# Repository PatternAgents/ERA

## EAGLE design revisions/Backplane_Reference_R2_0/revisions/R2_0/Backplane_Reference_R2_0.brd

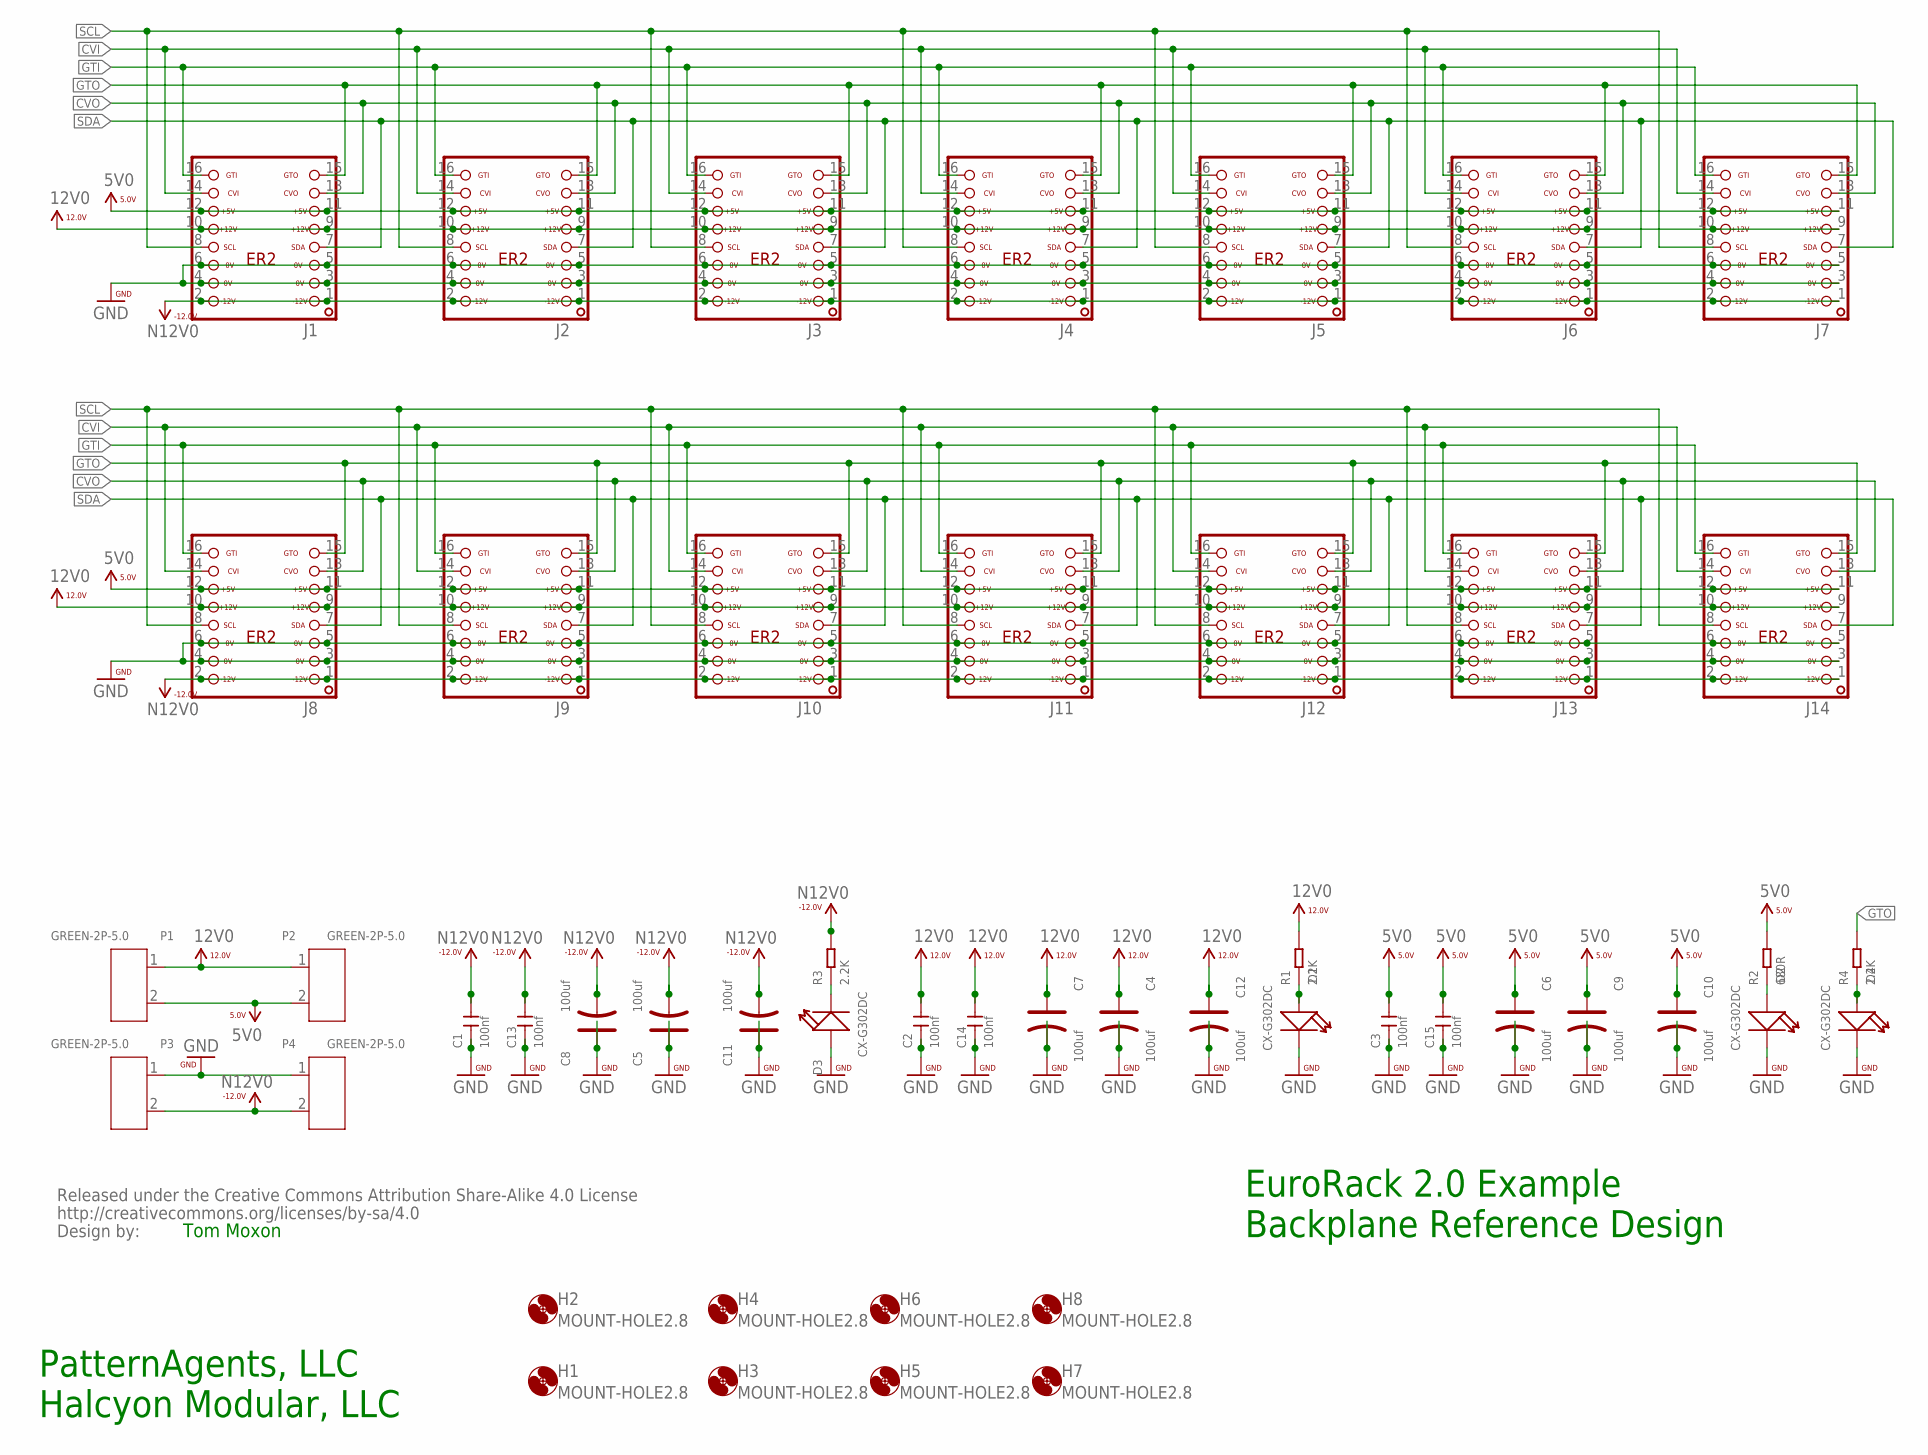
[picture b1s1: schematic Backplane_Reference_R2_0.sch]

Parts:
C1, C2, C3, C13, C14, C15: 100nf; CERAMIC-2.54
C4, C5, C6, C7, C8, C9, C10, C11, C12: 100uf; PC-D5.3MM
D1, D2, D3, D4: CX-G302DC; LED2-2.54-D3.0MM
H1, H2, H3, H4, H5, H6, H7, H8: MOUNT-HOLE2.8; 2,8
J1, J2, J3, J4, J5, J6, J7, J8, J9, J10, J11, J12, J13, J14: ER2-SHROUD; ER2
P1, P2, P3, P4: GREEN-2P-5.0; H2-5.0-10.5X8.0MM
R1, R3, R4: 2.2K; PR-D2.3XL6.5MM
R2: 680R; PR-D2.3XL6.5MM
U$48: BY_CC_SA_TEXTTEXT; BY_CC_SA_TEXT

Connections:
5V0: C3.2, C6.+, C9.+, C10.+, C15.2, J1.11, J1.12, J2.11, J2.12, J3.11, J3.12, J4.11, J4.12, J5.11, J5.12, J6.11, J6.12, J7.11, J7.12, J8.11, J8.12, J9.11, J9.12, J10.11, J10.12, J11.11, J11.12, J12.11, J12.12, J13.11, J13.12, J14.11, J14.12, P1.2, P2.2, R2.2
12V0: C2.2, C4.+, C7.+, C12.+, C14.2, J1.9, J1.10, J2.9, J2.10, J3.9, J3.10, J4.9, J4.10, J5.9, J5.10, J6.9, J6.10, J7.9, J7.10, J8.9, J8.10, J9.9, J9.10, J10.9, J10.10, J11.9, J11.10, J12.9, J12.10, J13.9, J13.10, J14.9, J14.10, P1.1, P2.1, R1.2
CVI: J1.14, J2.14, J3.14, J4.14, J5.14, J6.14, J7.14, J8.14, J9.14, J10.14, J11.14, J12.14, J13.14, J14.14
CVO: J1.13, J2.13, J3.13, J4.13, J5.13, J6.13, J7.13, J8.13, J9.13, J10.13, J11.13, J12.13, J13.13, J14.13
GND: C1.1, C2.1, C3.1, C4.-, C5.+, C6.-, C7.-, C8.+, C9.-, C10.-, C11.+, C12.-, C13.1, C14.1, C15.1, D1.K (-), D2.K (-), D3.A (+), D4.K (-), J1.3, J1.4, J1.5, J1.6, J2.3, J2.4, J2.5, J2.6, J3.3, J3.4, J3.5, J3.6, J4.3, J4.4, J4.5, J4.6, J5.3, J5.4, J5.5, J5.6, J6.3, J6.4, J6.5, J6.6, J7.3, J7.4, J7.5, J7.6, J8.3, J8.4, J8.5, J8.6, J9.3, J9.4, J9.5, J9.6, J10.3, J10.4, J10.5, J10.6, J11.3, J11.4, J11.5, J11.6, J12.3, J12.4, J12.5, J12.6, J13.3, J13.4, J13.5, J13.6, J14.3, J14.4, J14.5, J14.6, P3.1, P4.1
GTI: J1.16, J2.16, J3.16, J4.16, J5.16, J6.16, J7.16, J8.16, J9.16, J10.16, J11.16, J12.16, J13.16, J14.16
GTO: J1.15, J2.15, J3.15, J4.15, J5.15, J6.15, J7.15, J8.15, J9.15, J10.15, J11.15, J12.15, J13.15, J14.15, R4.2
N12V0: C1.2, C5.-, C8.-, C11.-, C13.2, J1.1, J1.2, J2.1, J2.2, J3.1, J3.2, J4.1, J4.2, J5.1, J5.2, J6.1, J6.2, J7.1, J7.2, J8.1, J8.2, J9.1, J9.2, J10.1, J10.2, J11.1, J11.2, J12.1, J12.2, J13.1, J13.2, J14.1, J14.2, P3.2, P4.2, R3.2
unnamed: D3.K (-), R3.1
unnamed: D1.A (+), R1.1
unnamed: D2.A (+), R2.1
unnamed: D4.A (+), R4.1
SCL: J1.8, J2.8, J3.8, J4.8, J5.8, J6.8, J7.8, J8.8, J9.8, J10.8, J11.8, J12.8, J13.8, J14.8
SDA: J1.7, J2.7, J3.7, J4.7, J5.7, J6.7, J7.7, J8.7, J9.7, J10.7, J11.7, J12.7, J13.7, J14.7

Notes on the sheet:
EuroRack 2.0 Example Backplane Reference Design
PatternAgents, LLC Halcyon Modular, LLC
Tom Moxon

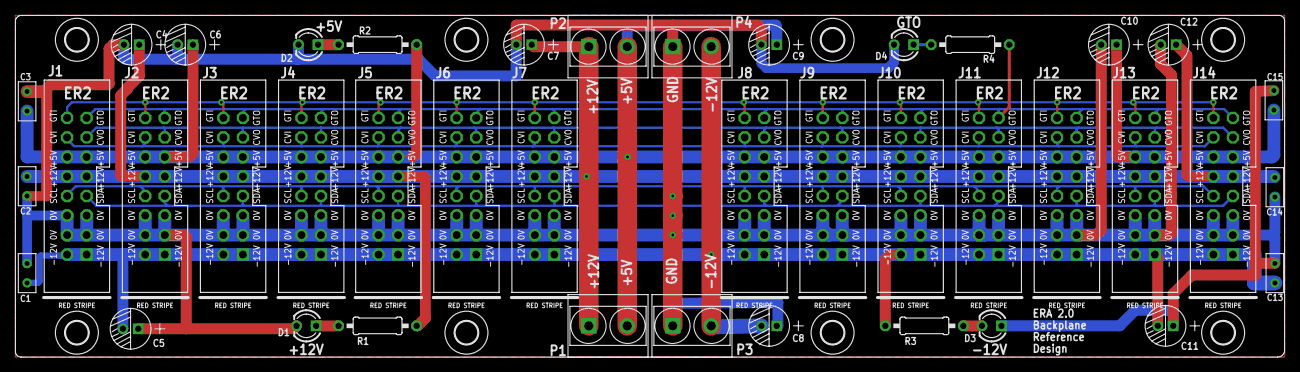
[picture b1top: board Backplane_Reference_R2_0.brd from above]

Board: 2 copper layers, 165.1 x 44.5 mm, 50 parts (0 on the bottom side), 14 nets.

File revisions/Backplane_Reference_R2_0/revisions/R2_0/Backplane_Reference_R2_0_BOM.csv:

6,100nf,DIP-CERAMIC-DISC-100NF-50V-Y5V(D5.0MM),CERAMIC-2.54,"C1, C2, C3, C13, C14, C15",302010208,CC1-F5SL2A101KSPW,100nf
9,100uf,DIP-ALUMINUM-100UF-16V(D5-H7MM),PC-D5.3MM,"C4, C5, C6, C7, C8, C9, C10, C11, C12",302030031,KS 100uF/16V,100uf
3,2.2K,DIP-RES-2.2K-5%-1/4W(PR-D2.3XL6.5MM),PR-D2.3XL6.5MM,"R1, R3, R4",301020010,FHCFR-1/4W-222J,2.2K
1,680R,DIP-RES-680R-5%-1/4W(PR-D2.3XL6.5MM),PR-D2.3XL6.5MM,R2,301020007,FHCFR-1/4W-681J,680R
4,CX-G302DC,DIP-LED-GREEN-GREEN(2P-D3MM),LED2-2.54-D3.0MM,"D1, D2, D3, D4",304090040,CX-G302DC,CX-G302DC
14,ER2-SHROUD,ER2-SHROUD,ER2-SHROUD,"J1, J2, J3, J4, J5, J6, J7, J8, J9, J10, J11, J12, J13, J14",302-S161,302-S161,302-S161
4,GREEN-2P-5.0,SCREW-TERMINAL-GREEN(2P-5.0),H2-5.0-10.5X8.0MM,"P1, P2, P3, P4",320110031,1935161,GREEN-2P-5.0

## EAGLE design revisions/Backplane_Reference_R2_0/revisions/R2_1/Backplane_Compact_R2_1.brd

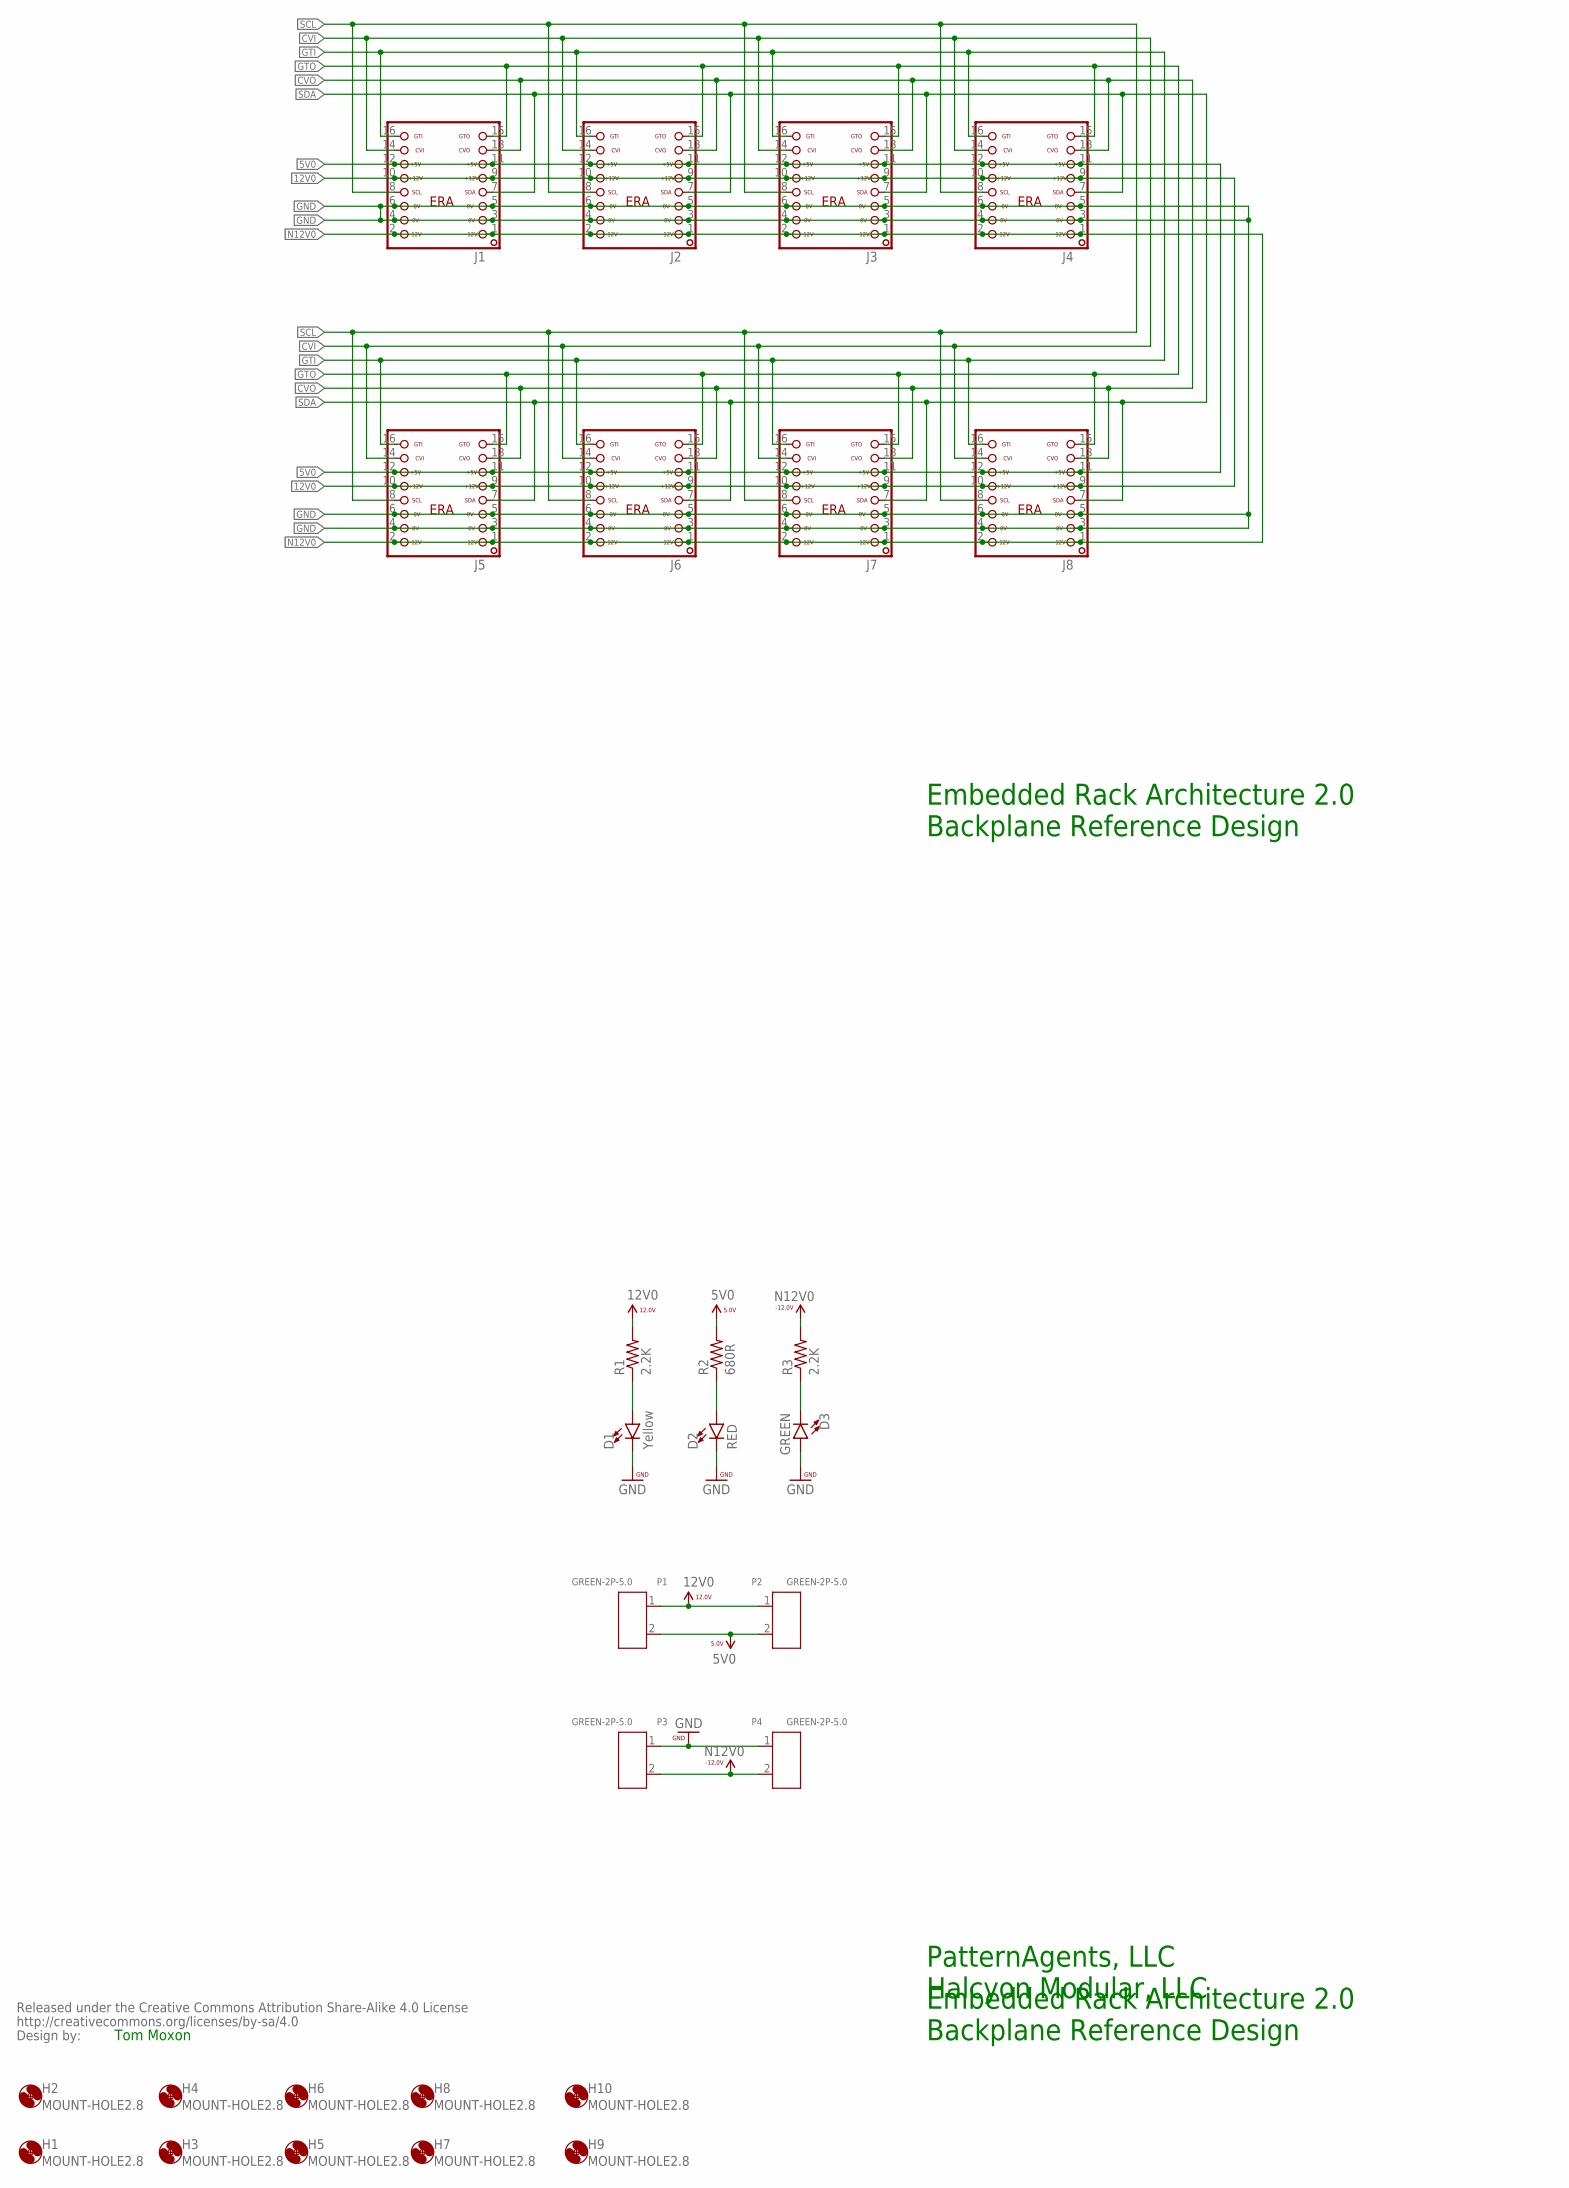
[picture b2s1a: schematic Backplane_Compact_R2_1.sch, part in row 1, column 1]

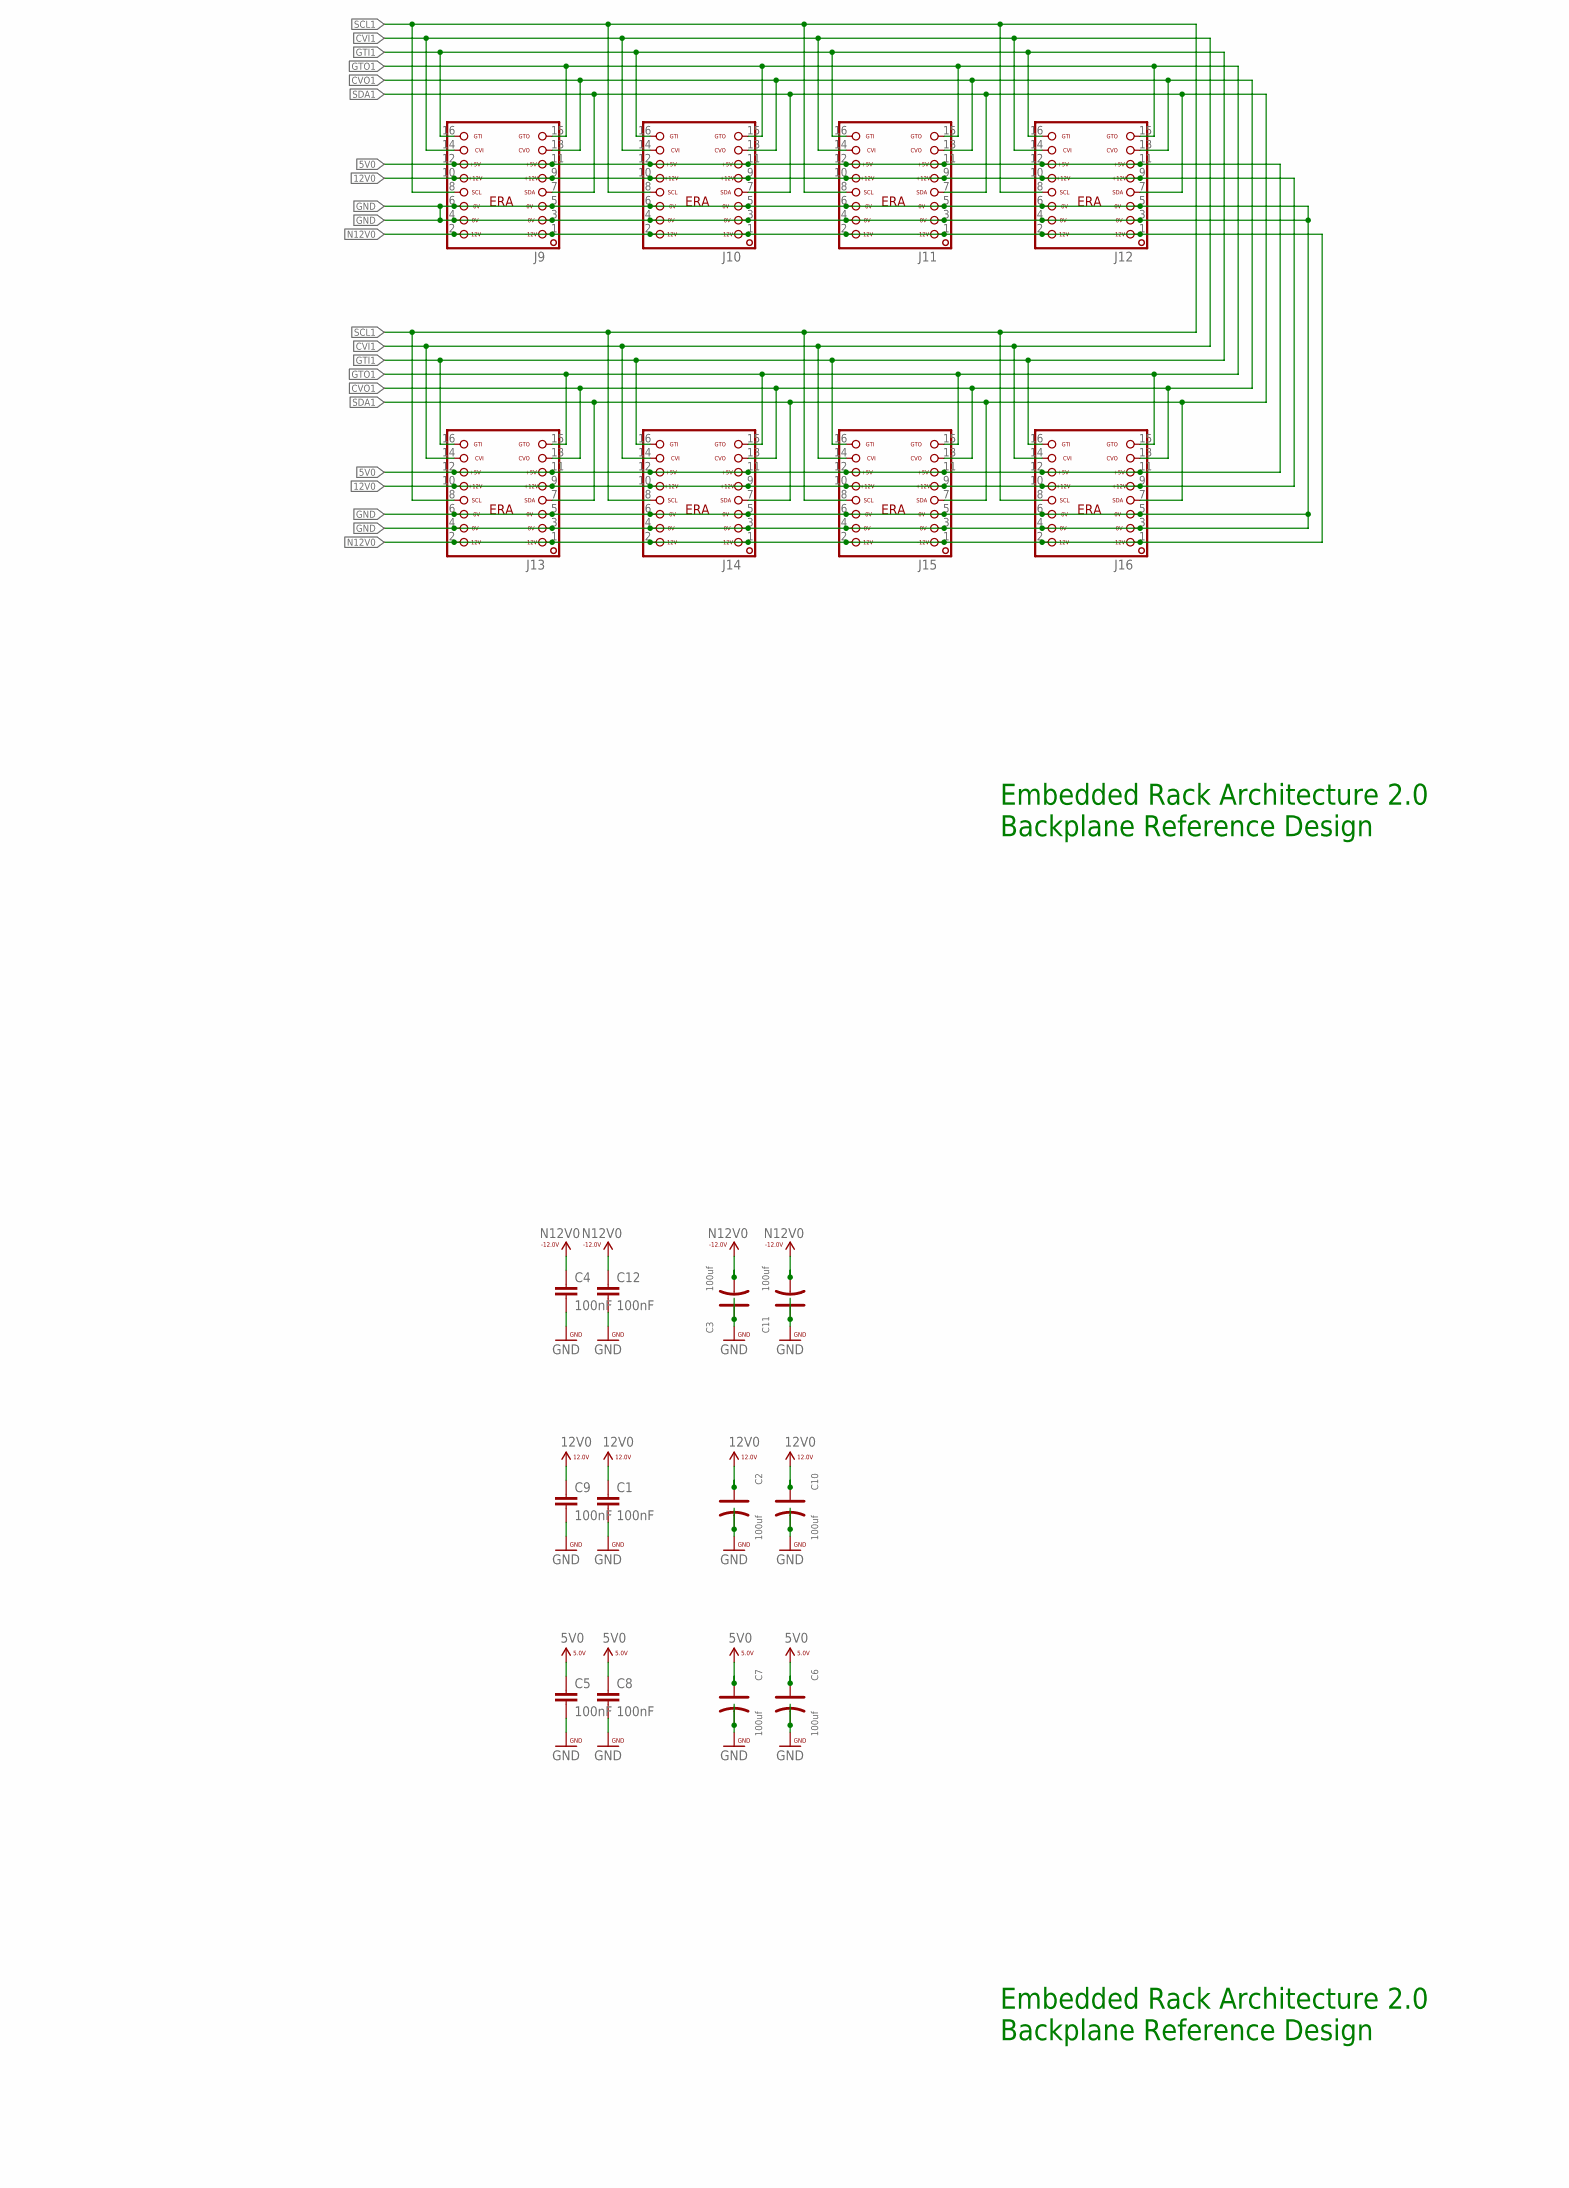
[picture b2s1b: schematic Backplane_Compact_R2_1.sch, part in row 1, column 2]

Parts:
C1, C4, C5, C8, C9, C12: 100nF; 0603-CAP
C2, C3, C6, C7, C10, C11: 100uf; PC-D5.3MM
D1: Yellow; LED-0603
D2: RED; LED-0603
D3: GREEN; LED-0603
H1, H2, H3, H4, H5, H6, H7, H8, H9, H10: MOUNT-HOLE2.8; 2,8
J1, J2, J3, J4, J5, J6, J7, J8, J9, J10, J11, J12, J13, J14, J15, J16: ERA-SHROUD; ERA
P1, P2, P3, P4: GREEN-2P-5.0; H2-5.0-10.5X8.0MM
R1, R3: 2.2K; 0603-RES
R2: 680R; 0603-RES
U$48: BY_CC_SA_TEXTTEXT; BY_CC_SA_TEXT

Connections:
5V0: C5.1, C6.+, C7.+, C8.1, J1.11, J1.12, J2.11, J2.12, J3.11, J3.12, J4.11, J4.12, J5.11, J5.12, J6.11, J6.12, J7.11, J7.12, J8.11, J8.12, J9.11, J9.12, J10.11, J10.12, J11.11, J11.12, J12.11, J12.12, J13.11, J13.12, J14.11, J14.12, J15.11, J15.12, J16.11, J16.12, P1.2, P2.2, R2.2
12V0: C1.1, C2.+, C9.1, C10.+, J1.9, J1.10, J2.9, J2.10, J3.9, J3.10, J4.9, J4.10, J5.9, J5.10, J6.9, J6.10, J7.9, J7.10, J8.9, J8.10, J9.9, J9.10, J10.9, J10.10, J11.9, J11.10, J12.9, J12.10, J13.9, J13.10, J14.9, J14.10, J15.9, J15.10, J16.9, J16.10, P1.1, P2.1, R1.2
CVI: J1.14, J2.14, J3.14, J4.14, J5.14, J6.14, J7.14, J8.14
CVI1: J9.14, J10.14, J11.14, J12.14, J13.14, J14.14, J15.14, J16.14
CVO: J1.13, J2.13, J3.13, J4.13, J5.13, J6.13, J7.13, J8.13
CVO1: J9.13, J10.13, J11.13, J12.13, J13.13, J14.13, J15.13, J16.13
GND: C1.2, C2.-, C3.+, C4.2, C5.2, C6.-, C7.-, C8.2, C9.2, C10.-, C11.+, C12.2, D1.C, D2.C, D3.A, J1.3, J1.4, J1.5, J1.6, J2.3, J2.4, J2.5, J2.6, J3.3, J3.4, J3.5, J3.6, J4.3, J4.4, J4.5, J4.6, J5.3, J5.4, J5.5, J5.6, J6.3, J6.4, J6.5, J6.6, J7.3, J7.4, J7.5, J7.6, J8.3, J8.4, J8.5, J8.6, J9.3, J9.4, J9.5, J9.6, J10.3, J10.4, J10.5, J10.6, J11.3, J11.4, J11.5, J11.6, J12.3, J12.4, J12.5, J12.6, J13.3, J13.4, J13.5, J13.6, J14.3, J14.4, J14.5, J14.6, J15.3, J15.4, J15.5, J15.6, J16.3, J16.4, J16.5, J16.6, P3.1, P4.1
GREEN: D3.C, R3.1
GTI: J1.16, J2.16, J3.16, J4.16, J5.16, J6.16, J7.16, J8.16
GTI1: J9.16, J10.16, J11.16, J12.16, J13.16, J14.16, J15.16, J16.16
GTO: J1.15, J2.15, J3.15, J4.15, J5.15, J6.15, J7.15, J8.15
GTO1: J9.15, J10.15, J11.15, J12.15, J13.15, J14.15, J15.15, J16.15
N12V0: C3.-, C4.1, C11.-, C12.1, J1.1, J1.2, J2.1, J2.2, J3.1, J3.2, J4.1, J4.2, J5.1, J5.2, J6.1, J6.2, J7.1, J7.2, J8.1, J8.2, J9.1, J9.2, J10.1, J10.2, J11.1, J11.2, J12.1, J12.2, J13.1, J13.2, J14.1, J14.2, J15.1, J15.2, J16.1, J16.2, P3.2, P4.2, R3.2
RED: D2.A, R2.1
SCL: J1.8, J2.8, J3.8, J4.8, J5.8, J6.8, J7.8, J8.8
SCL1: J9.8, J10.8, J11.8, J12.8, J13.8, J14.8, J15.8, J16.8
SDA: J1.7, J2.7, J3.7, J4.7, J5.7, J6.7, J7.7, J8.7
SDA1: J9.7, J10.7, J11.7, J12.7, J13.7, J14.7, J15.7, J16.7
YELLOW: D1.A, R1.1

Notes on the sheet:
Embedded Rack Architecture 2.0 Backplane Reference Design
PatternAgents, LLC Halcyon Modular, LLC
Tom Moxon

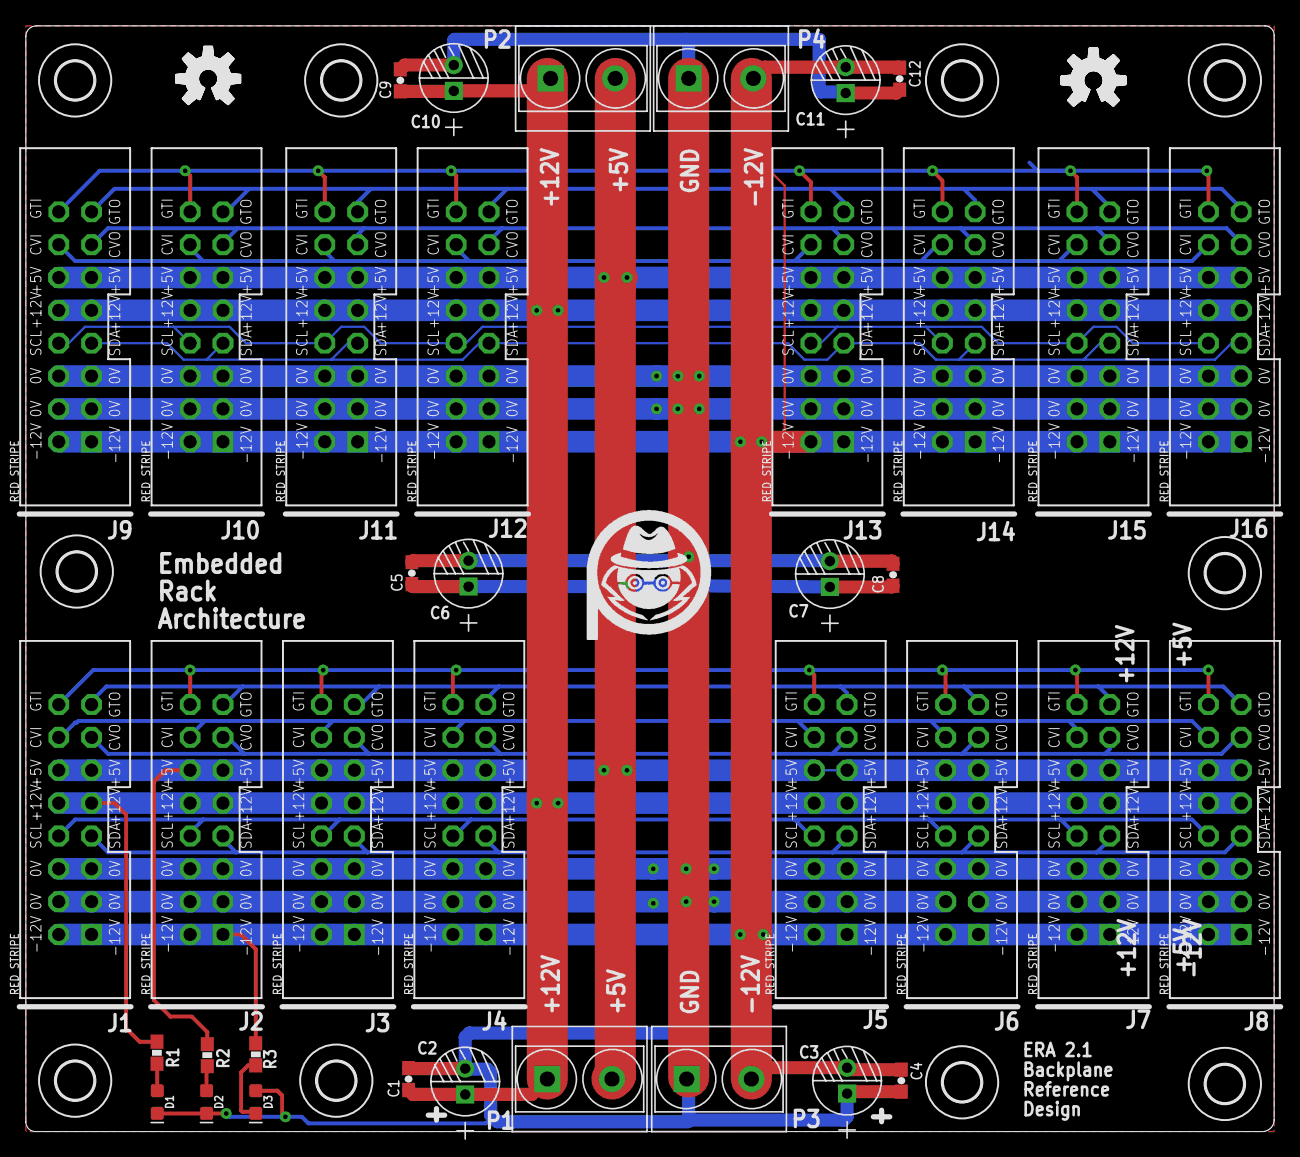
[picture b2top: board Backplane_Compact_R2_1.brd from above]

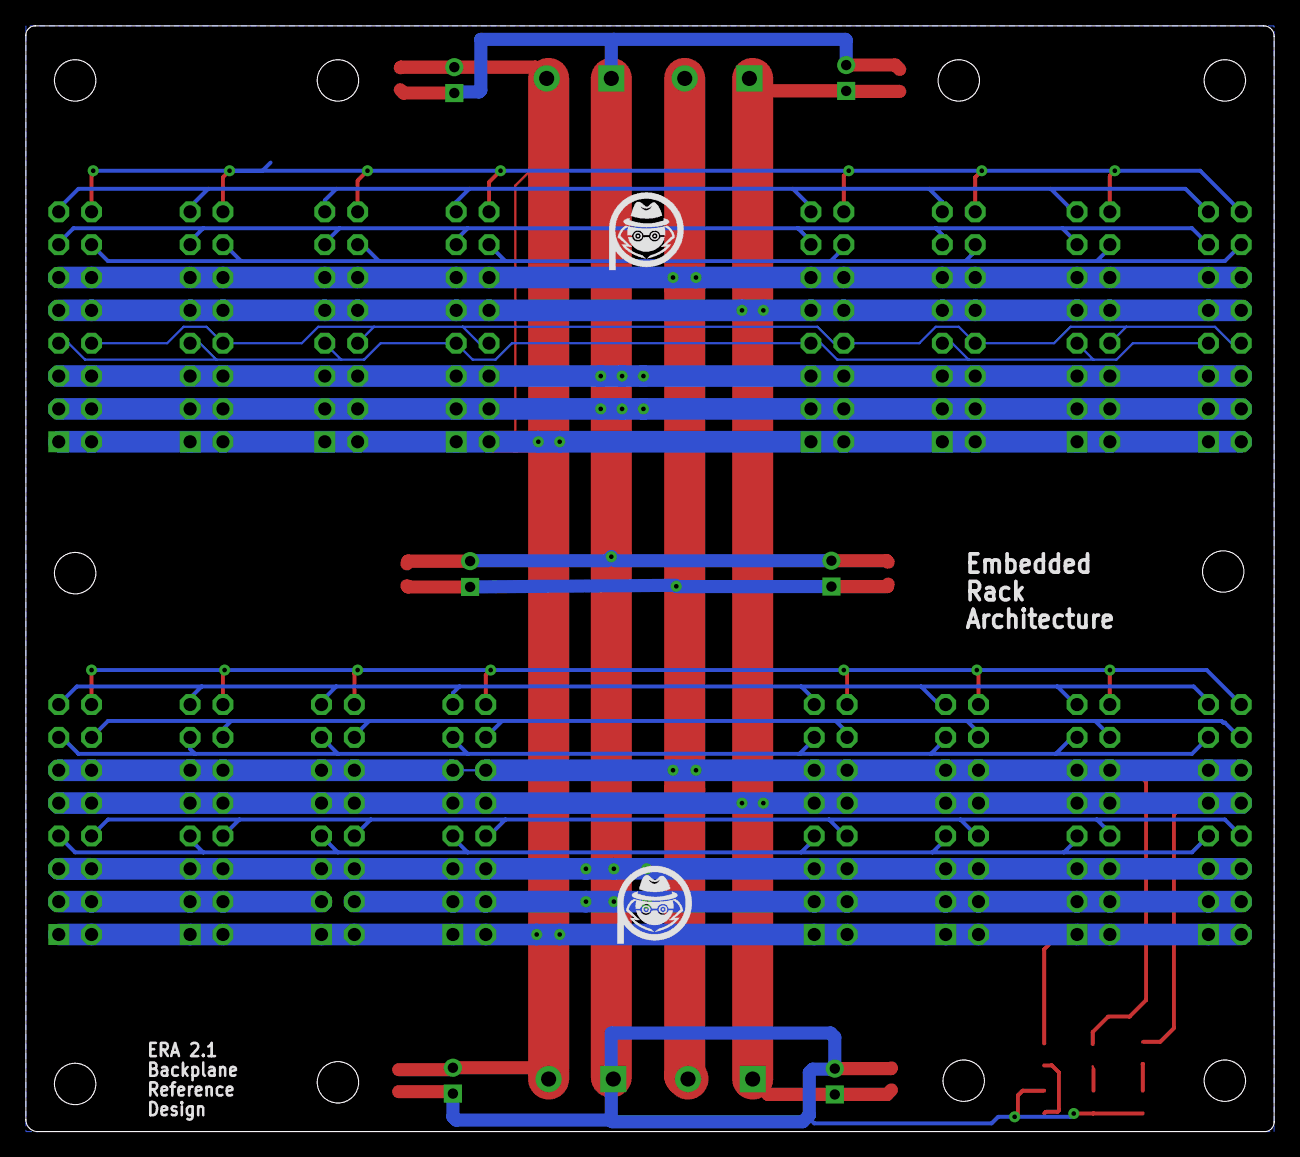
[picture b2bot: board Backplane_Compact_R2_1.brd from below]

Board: 2 copper layers, 96.5 x 85.5 mm, 56 parts (2 on the bottom side), 19 nets.

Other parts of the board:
U$7, U$8, U$9, U$36: OSHW_LOGO_MED_SYM
U$19, U$37: PA_LOGO_SYMMED; PA_LOGO_AGENT_MED_SYM
U$38: PA_LOGO_SYMLARGE; PA_LOGO_AGENT_LRG_SYM

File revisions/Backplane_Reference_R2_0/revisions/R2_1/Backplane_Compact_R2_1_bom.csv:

"Qty";"Value";"Device";"Package";"Parts";"Description";"";
"6";"100nF";"CAP0603-CAP";"0603-CAP";"C1, C4, C5, C8, C9, C12";"Capacitor";"";
"6";"100uf";"DIP-ALUMINUM-100UF-16V(D5-H7MM)";"PC-D5.3MM";"C2, C3, C6, C7, C10, C11";"302030031";"";
"2";"2.2K";"RESISTOR0603";"0603-RES";"R1, R3";"Resistor";"";
"1";"680R";"RESISTOR0603";"0603-RES";"R2";"Resistor";"";
"1";"BY_CC_SA_TEXTTEXT";"BY_CC_SA_TEXTTEXT";"BY_CC_SA_TEXT";"U$48";"BY_CC_SA_TEXT";"";
"16";"ERA-SHROUD";"ERA-SHROUD";"ERA";"J1, J2, J3, J4, J5, J6, J7, J8, J9, J10, J11, J12, J13, J14, J15, J16";"EuroRack2 - Backplane Connector";"";
"1";"GREEN";"LED-GREEN0603";"LED-0603";"D3";"Green SMD LED";"";
"4";"GREEN-2P-5.0";"SCREW-TERMINAL-GREEN(2P-5.0)";"H2-5.0-10.5X8.0MM";"P1, P2, P3, P4";"320110031";"";
"10";"MOUNT-HOLE2.8";"MOUNT-HOLE2.8";"2,8";"H1, H2, H3, H4, H5, H6, H7, H8, H9, H10";"MOUNTING HOLE with drill center marker";"";
"1";"RED";"LED-RED0603";"LED-0603";"D2";"Red SMD LED";"";
"1";"Yellow";"LED-YELLOW0603";"LED-0603";"D1";"Yellow SMD LED";"";

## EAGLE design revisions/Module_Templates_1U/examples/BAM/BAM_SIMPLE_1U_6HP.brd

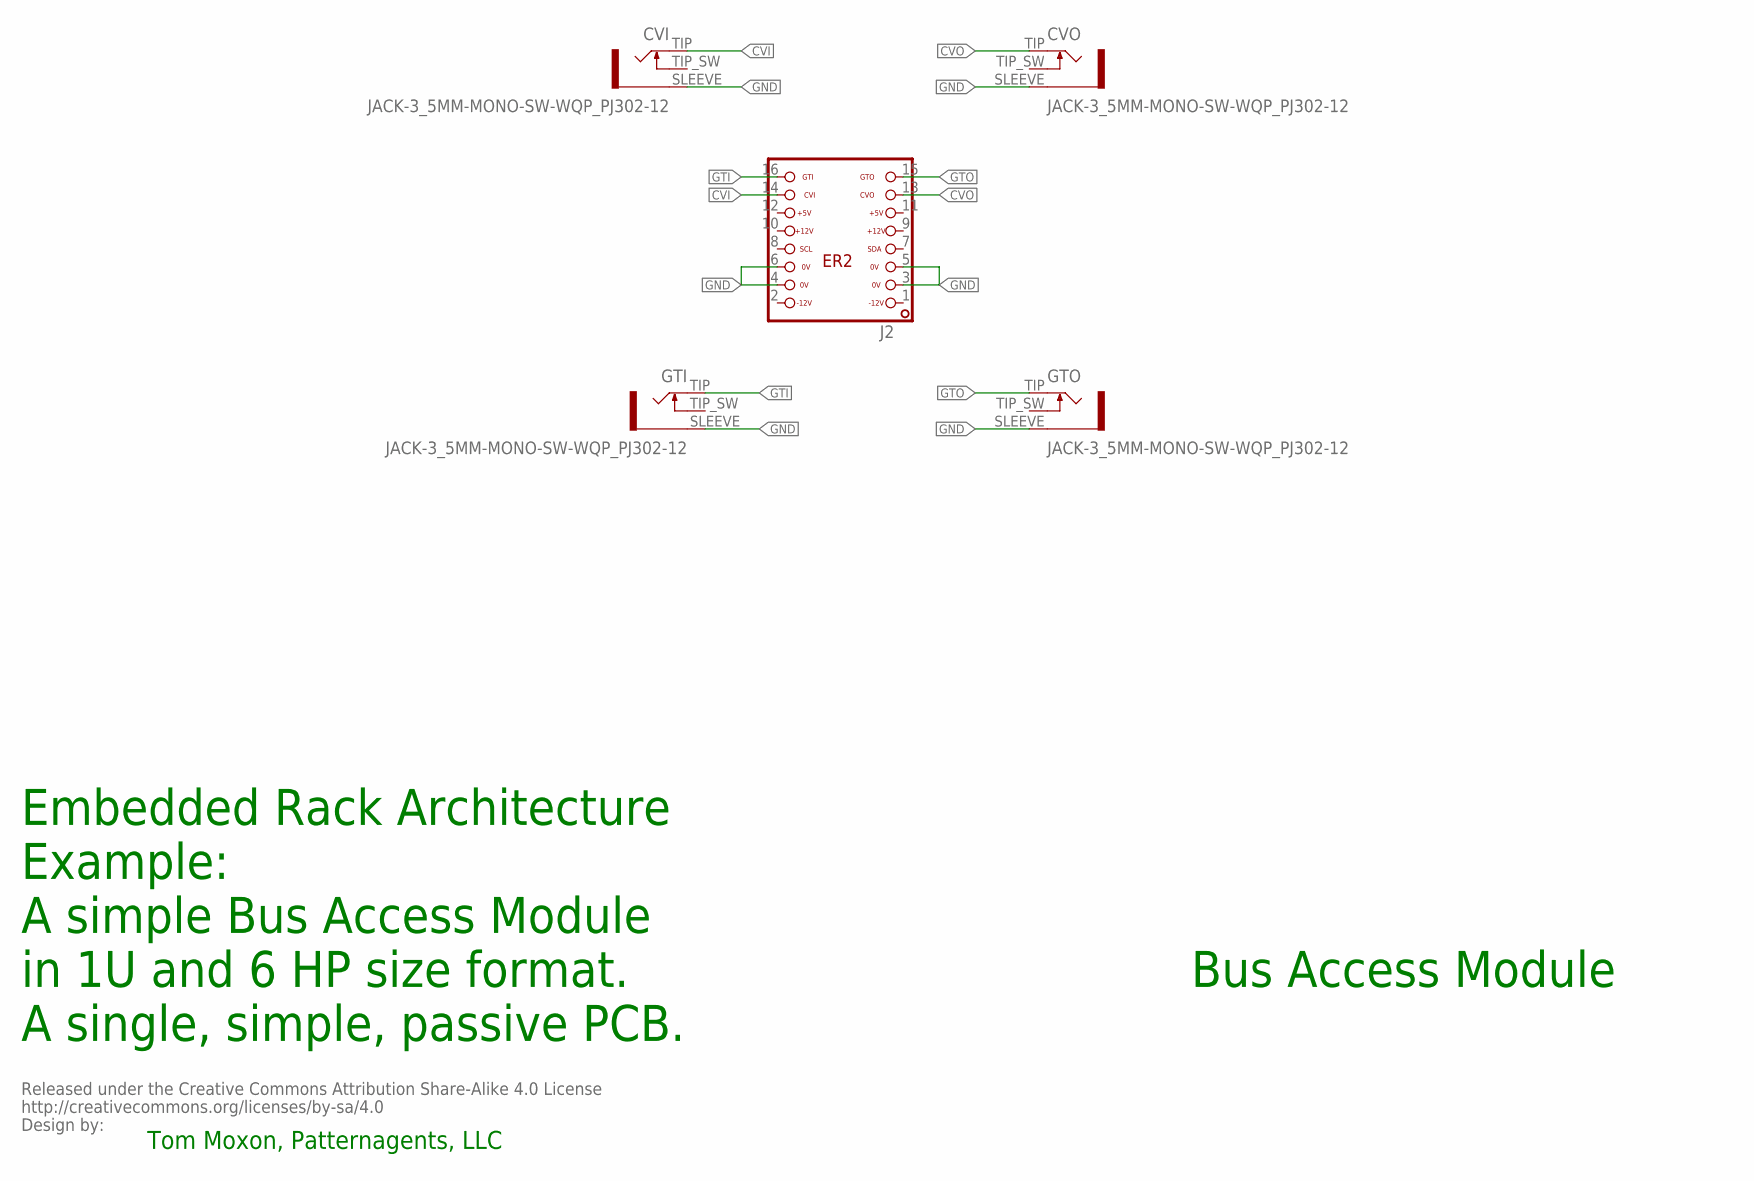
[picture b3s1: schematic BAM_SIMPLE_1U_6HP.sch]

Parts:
CVI: JACK-3_5MM-MONO-SW-WQP_PJ302-12; WQP_PJ301M-12
CVO: JACK-3_5MM-MONO-SW-WQP_PJ302-12; WQP_PJ301M-12
GTI: JACK-3_5MM-MONO-SW-WQP_PJ302-12; WQP_PJ301M-12
GTO: JACK-3_5MM-MONO-SW-WQP_PJ302-12; WQP_PJ301M-12
J2: ER2-SHROUD; ER2
TOMMOXON: BY_CC_SA_TEXTNULL; NULL_SYM

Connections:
CVI: CVI.TIP, J2.14
CVO: CVO.TIP, J2.13
GND: CVI.SLEEVE, CVO.SLEEVE, GTI.SLEEVE, GTO.SLEEVE, J2.3, J2.4, J2.5, J2.6
GTI: GTI.TIP, J2.16
GTO: GTO.TIP, J2.15

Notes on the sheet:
Bus Access Module
Embedded Rack Architecture Example: A simple Bus Access Module in 1U and 6 HP size format. A single, simple, passive PCB.
Tom Moxon, Patternagents, LLC

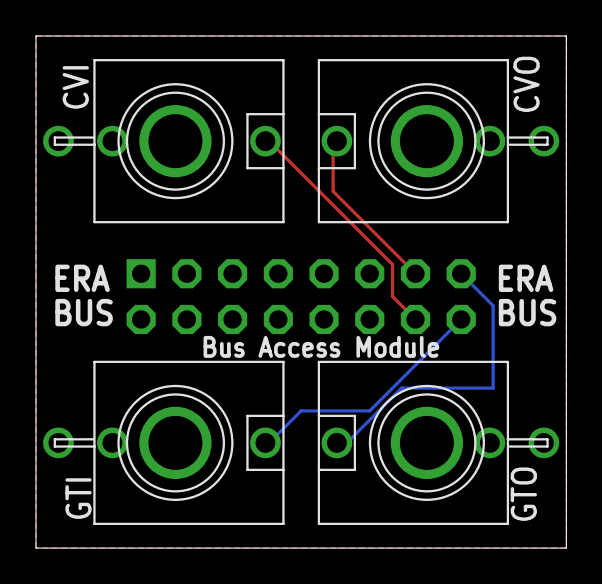
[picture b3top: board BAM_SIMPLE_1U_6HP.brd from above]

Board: 2 copper layers, 29.5 x 28.4 mm, 6 parts (1 on the bottom side), 5 nets.

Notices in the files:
parts and their libraries:
PatternAgents-Logos: License : http://creativecommons.org/licenses/by-sa/3.0
(Creative Commons 3.0)
PatternAgents-Logos: Source : http://wiki.creativecommons.org/CC_markers
PatternAgents-Logos: Released under the Creative Commons Attribution Share-Alike 4.0 License
